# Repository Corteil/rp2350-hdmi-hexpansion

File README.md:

# Hexi-GFX — RP2350 HDMI Hexpansion for the EMF Tildagon Badge

A Tildagon hexpansion that mirrors the EMF badge's 240×240 round screen onto a
real HDMI/DVI monitor — an RP2350 drives the video over HSTX, pixel-doubled and
pillarboxed into a standard 640×480@60 signal. Every existing badge app gets
HDMI output with no code changes.

For the full design rationale, bench measurements, BOM, costing, and the
phase-by-phase delivery plan that got here, see [`HISTORY.md`](HISTORY.md).
This file covers what's true *now*.

## Status (03/10/26)

**Real mirroring and stable HSTX video work together, confirmed on real
hardware** — not just clean logs, actual moving content on a monitor. Current
firmware is `firmware/pio-testcard/`, running on an **Adafruit Metro RP2350**
dev board wired to a real badge hexpansion port, and since 03/10/26 also on
a **Raspberry Pi Pico 2 + Adafruit DVI Sock** (`-DHEXI_BOARD=pico2`, see
[its section](#alternative-bench-board-raspberry-pi-pico-2--adafruit-dvi-sock-tested)),
powered straight from the badge's 3V3. The custom hexpansion PCB's
schematic is drafted in `hardware/`; layout hasn't started (see
[Next step](#next-step)).

- Badge side: `display.attach_mirror()`, from a fork of
  [hazanjon/badge-2024-software](https://github.com/hazanjon/badge-2024-software)
  PR #454, with three real bugs found and fixed (SPI acquire-bus timeout, a
  non-idempotent display init that froze the badge's own screen, and an
  SPI-host/GPIO-pin ordering bug). Fixes were merged into hazanjon's
  `feature/hdmi-mirror` branch as
  [hazanjon/badge-2024-software#1](https://github.com/hazanjon/badge-2024-software/pull/1);
  that branch was rebuilt and flashed to the badge on 03/10/26 and the
  mirror was confirmed working with the Pico 2.
- RP2350 side: a from-scratch PIO-based SPI0 slave receiver (the hardware
  SPI0/PL022 peripheral loses byte alignment mid-burst on this chip and never
  recovers), double-buffered HSTX/DVI scanout, and a grey-to-black vignette
  fade on the pillarbox/mask area around the circular content.
- Known, understood, non-blocking: ~12% of frames (Metro) to ~18% (Pico 2,
  one sample) get abandoned when the badge starts a new frame before the
  RP2350 finishes the previous one — benign, fully instrumented, not a bug
  to fix.
- Known, benign: on the Pico 2 each port insertion resets the board twice
  about 2 s apart (likely the badge power-cycling the port); the mirror
  re-attaches by itself. The relay app's 500 ms wait before its own reset
  pulse (raised from 100 ms) made the automatic reset noticeably more
  reliable.

## Repo layout

| Path | What it is |
|---|---|
| `firmware/pio-testcard/` | **Current firmware.** Real HSTX/DVI video and real SPI mirror reception together — what's actually flashed to the bench Metro RP2350 today. |
| `firmware/testcard/` | Earlier milestone: full hexpansion-identity EEPROM emulation + the first end-to-end SPI link demo. Superseded by `pio-testcard` for the mirror path itself, but still the reference for EEPROM emulation. |
| `firmware/pin-probe/` | Pico 2 bench tool that counts transitions on every header GPIO (read over SWD), used with the badge's Pin Tester app to prove which Pico pin each `HS_F`..`HS_I` wire lands on. |
| `firmware/mirror_debug/` | Bench diagnostic tool used to bring up the PIO-based SPI slave receiver protocol. |
| `firmware/phase0-*/` | Individual bring-up experiments from early de-risking (HSTX/DVI basics, colour-channel fix, SPI speed sweep, EEPROM emulation, ctx rasterisation benchmark, microSD). Each has its own README. |
| `hdmi-mirror-plan.md` | Implementation notes for switching to hazanjon's real `attach_mirror()` protocol (SPI mode, byte order, per-port pin overrides). Completed; kept for reference. |
| `hdmi-stills-mode-plan.md` | Proposal (not built): a high-resolution stills mode and a second-screen mode, one new `TDHS` frame type. |
| `HISTORY.md` | The full design journal — rationale, bench measurements, BOM, costing, risk register, phase plan. Read this for *why*, not *what's true now*. |
| `hardware/` | KiCad 10 project for the hexpansion PCB (schematic v0.1 done, layout not started), `lib/jlc.*` (JLCPCB/LCSC symbols, footprints and 3D models), and `hexpansion_bom.xlsx`, the JLCPCB assembly BOM tracker. |
| `tildagon-base/` | Tildagon KiCad symbol and footprint library (hexpansion edge connector etc.), used by `hardware/`. |
| `bom.csv` | Machine-readable bill of materials, generated from the schematic (LCSC numbers, JLC Basic/Extended, prices). |

## Hardware today

Bench rig: an Adafruit Metro RP2350 (SPI0 slave on GPIO20–23, HSTX on
GPIO12–19), wired to a real hexpansion port on an EMF Tildagon badge.

**HS wiring gotcha (all ports):** hazanjon's badge-side `PORT_PINS` table
puts SCK on `HS_G` and CS on `HS_H`, the opposite of this project's original
`HS_G`=CS / `HS_H`=SCK convention. For a real mirror test, wire
`HS_F`→GPIO20, `HS_G`→GPIO22, `HS_H`→GPIO21, `HS_I`→GPIO23 at the RP2350 end.
First found on port 4, since tested on all six ports; the PCB is wired this
way. See `HISTORY.md` §4.1 for the full derivation and why the two sides
disagree.

VID/PID assigned for the eventual EEPROM-emulating hexpansion: `0x1969` /
`0x4544`.

### Alternative bench board: Adafruit Feather RP2350 + HSTX (builds, not yet tested on hardware)

Build with `-DHEXI_BOARD=feather` (see [Building and flashing](#building-and-flashing)).
The Feather is an RP2350A: the same die as the RP2354A the real hexpansion
uses (the RP2354A just adds 2 MB of flash in the package), and
its 22-pin HSTX FPC connector carries GPIO12–19 in the same lane order the
firmware already uses. So video needs no changes: plug in the same DVI
breakout and FPC cable as on the Metro.

Two things do move. GPIO21 is the Feather's onboard NeoPixel and isn't
broken out, so the Metro's GPIO20–23 SPI block can't be used. The
PIO-based receiver doesn't need hardware-SPI pins, just three consecutive
GPIOs for MOSI/CS/SCK, so it moves to D9–D11:

| Function | RP2350 GPIO | Feather pin |
|---|---|---|
| HSTX video (all 8 lines) | 12–19 | 22-pin HSTX FPC connector |
| SPI MOSI (`HS_F`) | 9 | D9 |
| SPI CS (`HS_H` on port 4) | 10 | D10 |
| SPI SCK (`HS_G` on port 4) | 11 | D11 |
| SPI MISO (`HS_I`, never driven) | 20 | MI |
| EEPROM-emulation I2C0 SDA / SCL | 4 / 5 | GPIO4 (CircuitPython `D12`/`IO4`) / D5 |
| Debug UART0 TX / RX (`_debug` build) | 0 / 1 | TX / RX |
| Status NeoPixel | 21 | onboard |
| `LS_A` → RUN | — | RST |
| GND | — | GND |

The port-4 SCK/CS crossover is already applied above. GPIO4 is labelled
from CircuitPython's pin map, so check the board silkscreen for that pad.
SWD is on the Feather's 3-pin JST-SH connector, so the Debug Probe cable
plugs straight in. UF2 flashing (hold BOOT, tap RESET) also works. Flash
is 8 MB, not 16 MB, which is plenty for this firmware. Use the RESET
button for step 3 of the manual reinsertion method below.

### Alternative bench board: Raspberry Pi Pico 2 + Adafruit DVI Sock (tested)

Build with `-DHEXI_BOARD=pico2`. **Confirmed working end to end on 03/10/26**:
stable mirror picture on the official Raspberry Pi monitor, status LED at
5 Hz while frames arrive. The Pico 2 is an RP2350A, so HSTX reaches the same
GPIO12–19 block the [Adafruit DVI Sock for Pico](https://www.adafruit.com/product/5957)
is wired to. The Sock is a passive connector plus 220 Ω series resistors, and
its product page describes it for the RP2040. It works fine with HSTX, but its
**lane order differs from the Metro/Feather wiring**, so this variant uses
`lane_to_output_bit = {0, 6, 4}` (D0 = GP12/13, D1 = GP18/19, D2 = GP16/17,
CK = GP14/15, "+" on the even GPIO).

| Function | RP2350 GPIO | Notes |
|---|---|---|
| HSTX video | 12–19 | DVI Sock, see lane order above |
| SPI MOSI (`HS_F`) | 0 | |
| SPI CS (`HS_H` on port 4) | 1 | |
| SPI SCK (`HS_G` on port 4) | 2 | port-4 SCK/CS crossover already applied |
| SPI MISO (`HS_I`, never driven) | 3 | |
| EEPROM-emulation I2C0 SDA / SCL | 4 / 5 | unchanged |
| 5V boost enable (active-high) | 6 | off at boot; the badge switches it, see [5V boost switch](#5v-boost-switch-added-151026) |
| Debug UART1 TX / RX (`_debug` build) | 8 / 9 | moved off GP0/1, which are now SPI inputs |
| Status LED (plain GPIO) | 25 | 1 Hz = running, no frames; 5 Hz = frames arriving |
| Status NeoPixel (external WS2812) | 22 | same colours as the other boards |
| `LS_A` → `RUN` | — | lets the badge reset the Pico 2; a reset switch from `RUN` to GND is also fitted |
| Badge 3V3 → VSYS (pin 39) | — | powers the board, with no USB attached |
| GND | — | shared with the badge: any GND pin on the port breakout hexpansion |

A step-by-step hardware build and flashing guide for this variant is in
[`docs/index.md`](docs/index.md), also published at
<https://corteil.github.io/rp2350-hdmi-hexpansion/>. A prebuilt UF2 is on the
[`pico2-v3` release](https://github.com/Corteil/rp2350-hdmi-hexpansion/releases/tag/pico2-v3).

Notes from bring-up:

- **Power:** it runs fine from the badge's 3V3 with no USB. Never connect USB
  and an external 3V3 into VSYS together: VBUS feeds VSYS through a diode, so
  the external source gets back-fed. Use a series Schottky if both are needed.
- **5 V on the Sock's 5 V pad** is monitor-dependent. Some monitors only show
  a signal when it is present; the official Raspberry Pi monitor and a video
  capture dongle don't need it. With no USB attached there is no VBUS, so for
  a monitor that needs it, use a boost converter: input from VSYS and GND,
  5 V output to the Sock's 5 V pad, GND common with the port breakout's GND.
- **Each port insertion resets the Pico 2 twice, about 2 s apart** (probably
  the badge power-cycling the port; not scoped). It is harmless: the mirror
  re-attaches and the picture returns by itself.
- **Wire-continuity check:** `firmware/pin-probe` plus Pin Tester's `blink`
  (via `mpremote exec`, store-installed path `/apps/Corteil_Pin_Tester`) maps
  each badge pin to a Pico GPIO. A bad `HS_F` wire here looked like CS/SCK
  arriving but a stuck-high or stuck-low data line and no `TDHD` match.

### Alternative bench board: Waveshare RP2350-PiZero (not yet tested)

The [Waveshare RP2350-PiZero](https://www.waveshare.com/wiki/RP2350-PiZero)
can stand in for the Metro, with one big caveat: its onboard mini-HDMI is
wired to **GPIO32–39**, and HSTX only reaches **GPIO12–19**, so the current
firmware can't drive the onboard connector. Instead, wire HSTX from the
40-pin header to an external DVI breakout, exactly as on the Metro.

Its chip (RP2350B), flash (W25Q128, 16 MB) and 12 MHz crystal match the
Metro, and every pin the firmware uses is on the header. The existing
`pio_testcard` build should therefore run unmodified, but that hasn't been
checked on real hardware yet.

**The header is not Raspberry-Pi numbered.** Waveshare's J5 net labels are
RP2350 GPIOs and differ from the silkscreen/BCM names (e.g. header pin 7 is
BCM4 but RP2350 **GPIO14**). Wire by *header pin number* from this table,
taken from Waveshare's schematic (`RP2350-PiZero.pdf`):

| Function | RP2350 GPIO | PiZero header pin |
|---|---|---|
| HSTX D2+ / D2− | 12 / 13 | 21 / 33 |
| HSTX CLK+ / CLK− | 14 / 15 | 7 / 29 |
| HSTX D1+ / D1− | 16 / 17 | 36 / 11 |
| HSTX D0+ / D0− | 18 / 19 | 12 / 35 |
| SPI MOSI (`HS_F`) | 20 | 38 |
| SPI CS (`HS_H` on port 4) | 21 | 40 |
| SPI SCK (`HS_G` on port 4) | 22 | 15 |
| SPI MISO (`HS_I`) | 23 | 16 |
| EEPROM-emulation I2C0 SDA / SCL | 4 / 5 | 8 / 10 |
| Debug UART0 TX / RX (`_debug` build) | 0 / 1 | 27 / 28 |
| GND | — | 6, 9, 14, 20, 25, 30, 34, 39 |
| `LS_A` → RUN | — | not on the header: solder to the RUN side of the reset button (Key2) |

HSTX lane assignment comes from `hstx_dvi_init()` in
`firmware/pio-testcard/src/main.c` (`lane_to_output_bit`), and the port-4
SCK/CS crossover above is already applied. Other differences from the Metro:

- **No addressable RGB LED.** The only LED is a red power LED. The firmware
  still drives its status-LED signal on GPIO25 (header pin 22). That's
  harmless, and you can wire a WS2812 there to get the status colours back.
- **SD card-detect isn't on a GPIO** (the slot's CD pin goes to GND), so
  GPIO22 is free for SCK.
- **Buttons:** Key1 is BOOTSEL and Key2 is reset (RUN). Use Key2 for step 3
  of the manual reinsertion method below.
- **SWD** is on the 3-pin header H1 (SWCLK / GND / SWDIO), so Debug Probe
  flashing works as documented. Holding Key1 while plugging in USB and
  copying `pio_testcard.uf2` also works.
- **Don't switch the build to the Pico SDK's `waveshare_rp2350_pizero` board
  file** without overriding its default UART. It puts UART1 on GPIO4/5,
  which collides with the EEPROM-emulation I2C in the `_debug` build. The
  Metro board file already used here puts UART0 on GPIO0/1.
- **Signal integrity:** the TMDS pairs are spread across the header, so they
  run at 252 Mbit/s over hand-run wires rather than an FPC cable. Keep each
  +/− pair short, equal-length and twisted together. Suspect the wiring
  first if the picture sparkles or drops out.

Using the onboard mini-HDMI would need one of two things. One is a PIO-based
PicoDVI scanout: 252 MHz `clk_sys`, a PIO block set to see GPIO16–47, and a
reworked framebuffer. The other is a board mod: remove the eight 200 Ω
series resistors (R1–R4, R6, R7, R10, R12) and feed GPIO12–19 into their
connector-side pads. Neither has been tried. The first diverges from the
HSTX design the hexpansion PCB will use.

## Reinsertion procedure (automatic since 11/10/26; manual fallback below)

Plugging the hexpansion into a running badge now brings the mirror up by
itself. The relay app packed into the fake EEPROM
(`firmware/testcard/badge_app/app.py`) runs on every insertion: it waits
500 ms for the connector to settle, pulses `LS_A` low for 10 ms to
hardware-reset the RP2350 (`LS_A` is wired to `RUN`), waits 1.5 s for it to
reboot, then calls `display.attach_mirror()`. See
`firmware/pio-testcard/src/main.c`'s own comments for the root-cause trail
on why a reset is needed at all.

- **Auto-attach setting.** The relay app reads the badge's
  `hdmi_auto_attach` setting (default on when unset) and skips both the
  reset and the attach when it's off. The setting is shared with
  [tildagon-hdmi-manager](https://github.com/Corteil/tildagon-hdmi-manager)
  (Info tile) and can also be toggled on the relay app's own screen (OK).
  Turning it on from the relay screen runs the same reset-then-attach.
- **Relay screen.** It shows `HDMI-HEX`, a live status from
  `display.is_mirror_active()` (green Mirroring, amber starting... / Not
  mirroring, red on failure, in the same colours as tildagon-hdmi-manager),
  the Auto-attach and 5V boost settings, and a key list (hexagonal buttons;
  OK is `C` and Cancel is `F` on this badge):

  | Key | Does |
  |---|---|
  | `B` | Toggle the 5V boost |
  | `C` | Toggle auto-attach (turning it on runs reset-then-attach) |
  | `D` | Attach / detach the mirror. Attaching does the reset first; detaching doesn't |
  | `F` | Back |

  Both the status and the reset need badge firmware with the display-mirroring
  patch; stock firmware has no `attach_mirror()`, so there the hexpansion is
  recognised but never mirrors.
- **In tildagon-hdmi-manager**, OK on the Status tile does the same
  detach, reset, wait, attach sequence on demand.

### 5V boost switch (added 15/10/26)

A 3V3→5V boost converter supplies the HDMI connector's +5V pin. Switching it
off saves power, so it is controlled from the badge:

- **Firmware.** `firmware/pio-testcard` drives the boost enable on GPIO6
  (`PIN_BOOST_EN` in `main.c`, active-high) from one control byte in the
  emulated EEPROM at address `0x20` (`EEPROM_CTRL_BOOST_EN`, bit 0; see
  `eeprom_i2c.h`). That is the gap between the 32-byte header and the
  filesystem at `0x40`, outside the header checksum. The badge reads and
  writes it as an ordinary EEPROM access at I2C address `0x50` with a 16-bit
  address. **The boost is off at boot and after every reset.**
- **Setting.** The badge-side setting is `hdmi_boost` (default on when unset),
  shared by the relay app (`B`) and tildagon-hdmi-manager (Info tile, "5V
  boost"). Both write the saved value to the firmware just before attaching and
  after each reset, so the boost comes on a moment after a reset and a
  setting of off stays off. With no badge app involved the +5V pin stays off,
  which some monitors may not tolerate.
- **Pin.** GPIO6 is the bench wiring. The planned PCB (pin map below, and
  `HISTORY.md`) puts the boost enable on GPIO29 and the Qwiic I2C1 on GPIO6/7,
  so `PIN_BOOST_EN` will need to follow whichever the board uses.

### Manual method (fallback)

If `LS_A` isn't wired to `RUN`, or the automatic reset misses, the original
manual sequence still works:

1. Insert the `HDMI-HEX` hexpansion.
2. In `tildagon-hdmi-manager` (or `display_manager`), **detach** the mirror.
3. Press the physical **reset button** on the RP2350 board (SW2 on the
   Metro; the reset button on your board otherwise).
4. **Attach** the mirror again from the same app.

The order matters: the reset goes between detach and attach, not after.

## Building and flashing

### RP2350 firmware (`pio-testcard`)

Needs the Raspberry Pi Pico SDK (2.x) and an `arm-none-eabi-gcc` toolchain,
with `PICO_SDK_PATH` set.

```sh
cd firmware/pio-testcard
mkdir -p build && cd build
cmake ..
cmake --build .
```

That builds for the Metro RP2350 (the default). For the Adafruit Feather
RP2350 + HSTX, configure a separate build directory from
`firmware/pio-testcard` instead:

```sh
cmake -B build-feather -DHEXI_BOARD=feather
cmake --build build-feather
```

For the Raspberry Pi Pico 2 + Adafruit DVI Sock, use `-DHEXI_BOARD=pico2`
the same way (`cmake -B build-pico2 -DHEXI_BOARD=pico2`).

Flash over SWD with a Raspberry Pi Debug Probe:

```sh
openocd -f interface/cmsis-dap.cfg -f target/rp2350.cfg -c "adapter speed 5000" \
  -c "program pio_testcard.elf verify reset exit"
```

### Badge-side driver

Depends on `display.attach_mirror()` from the fork above. Built via the
project's own Docker image (`ghcr.io/emfcamp/esp_idf:v5.5.1`):

```sh
git clone --recursive --branch pr-454-hazan-mirror https://github.com/Corteil/badge-2024-software.git
cd badge-2024-software
./scripts/firstTime.sh
docker run --rm --env "TARGET=esp32s3" -v "$(pwd)":/firmware -u "$(id -u):$(id -g)" \
  -e HOME=/tmp ghcr.io/emfcamp/esp_idf:v5.5.1
```

Flash to a real badge in bootloader mode (disconnect USB, hold **BAT + BOOP**
for ~20s, reconnect):

```sh
docker run --rm --device /dev/ttyACM0:/dev/ttyUSB0 --group-add <your dialout/plugdev GID> \
  --env "TARGET=esp32s3" -v "$(pwd)":/firmware -u "$(id -u):$(id -g)" -e HOME=/tmp \
  ghcr.io/emfcamp/esp_idf:v5.5.1 deploy
```

The badge stays in bootloader mode after flashing — disconnect/reconnect the
USB cable once more to actually boot the new image.

## Next step

Designing the actual hexpansion PCB (44 mm hexagon, EEPROM emulation, USB-C +
HDMI power isolation) — the whole plan for it, including the pin map, power
architecture, BOM, and costing this bench work was de-risking, is in
[`HISTORY.md`](HISTORY.md).

**Schematic v0.1 is done** (`hardware/rp2350-hdmi-hexpansion.kicad_sch`,
28/09/26). The PCB layout hasn't started: open the project and run
*Tools → Update PCB from Schematic*. Every part has a JLCPCB/LCSC number,
and its symbol, footprint and 3D model are in the project library
`hardware/lib/jlc.*`, pulled with
[easyeda2kicad](https://github.com/uPesy/easyeda2kicad.py). KiCad's ERC is
clean apart from one expected warning (HEXP_DET tied to GND is how the
badge detects a hexpansion), and the exported netlist was checked
pin-for-pin against the design. `bom.csv` and `hardware/hexpansion_bom.xlsx`
are generated from the schematic.

Changes from the `HISTORY.md` plan:

- **MCU is the RP2354A**, not the RP2350A: the same die and QFN-60 pinout,
  with 2 MB of flash in the package on QSPI CS0. There's no external flash
  chip (the W25Q128 is gone). 2 MB is plenty: the largest firmware build is
  about 260 KB. Build with `PICO_FLASH_SIZE_BYTES` set to 2 MB.
- **The PSRAM is footprint-only (DNP)**, for optional hand soldering. The
  part is the **APS6404L-3SQR-SN** (SOP-8, 3.3 V); the `-ZR` that the old
  BOM listed is USON-8. It stays on QSPI CS1 = GPIO0, with a 10k pull-up on
  CS that is fitted even when the PSRAM isn't, so firmware must detect it
  at boot rather than assume it.
- **Full-size HDMI Type A** socket instead of mini-HDMI. It's wider, so check
  the fit on the outer flat.
- **One Qwiic socket** instead of two, to save edge space.
- **TLV62569** 2 A buck instead of the TPS62203 (300 mA, poor stock).
- **No HDMI DDC/EDID.** The output is always 640×480@60, which every
  monitor must accept, so there's nothing to read. The PCA9306 and its six
  passives are gone. Hot-plug detect stays (GPIO2).
- **No microSD.** That frees the second side flat and GPIO5 and 8–11.
  Spare GPIOs are now **3, 4, 5, 8, 9, 10, 11**, all left no-connect.
- **Trimmed to the Raspberry Pi minimal design.** TMDS lines go straight
  from GPIO12–19 to the ESD chips and socket, with no 0R insurance resistors,
  as the bench has always run. There are 7 × 100 nF on 3.3 V (pins 44/45 and
  53/54 share, as in Raspberry Pi's reference), no BOOTSEL pull-up (QSPI_SS
  has one internally) and no RUN debounce cap. The ferrite beads are gone.
- Kept from the design guide: the 1k crystal series resistor, 33R
  VREG_AVDD filter, 27R USB series resistors and a 10k RUN pull-up (because
  of the badge reset). Also added: an HDMI +5V PTC fuse and test pads.
- Result: **80 JLC-placed parts, about $5.11 a board** at the 10-board price
  tier (25 capacitors, 32 resistors).

**Pin map changes from `HISTORY.md` §4.1.** It had no free GPIOs for three
signals, so `LS_C`/`LS_D`/`LS_E` are left unconnected and their GPIOs reused:

| GPIO | Now | Was |
|---:|---|---|
| 27 | SK6805 RGB LED data | `LS_C` (bootloader-entry idea) |
| 28 | Badge-rail sense (ADC2, 100k/100k from `3V3_BADGE`) | `LS_D` spare |
| 29 | HDMI +5V boost enable (100k pull-down) | `LS_E` spare |

On the board, `HS_G`→GPIO22 (SCK) and `HS_H`→GPIO21 (CS). That's the
crossing the badge's mirror driver needs, **tested on all six ports**.

**Firmware changes the PCB needs** (from `pio-testcard`): EEPROM emulation
moves from GPIO4/5 to **GPIO24/25**, with its internal pull-ups *off*
(they'd back-power an unpowered badge). The status NeoPixel moves to
**GPIO27**. Set the flash size to 2 MB.

**Badge reset without backfeed.** `LS_A` drives RUN through **U11, an
SN74LVC1G07 open-drain buffer powered from `3V3_BADGE`**. R4 (10k to
`3V3_BADGE`) holds `LS_A` high, so it idles at "not reset". When the badge
is off, U11 is unpowered. Its partial-power-down (I_off) spec, ≤10 µA and
typically far less, stops the RUN pull-up leaking into the badge, and the
RP2354A keeps running from USB. A plain diode can't do this: the reset
current and the leak flow the same way.

## Acknowledgements

This project depends on the work of [hazanjon](https://github.com/hazanjon).
The badge-side display mirroring that the hexpansion receives, including
`display.attach_mirror()`, the SPI frame protocol with its `TDHD` header, and
the per-port pin handling in `flow3r_bsp_display_mirror.c`, comes from
his [badge-2024-software](https://github.com/hazanjon/badge-2024-software)
work (PR #454 against `emfcamp/badge-2024-software`). His
[display_manager](https://github.com/hazanjon/display_manager) app provides
the badge-side driver definitions and attach controls used to drive it.
Without that groundwork there would be nothing for this hexpansion to mirror,
and the fixes in this repo's badge-side PR were built on top of it. Thank you.

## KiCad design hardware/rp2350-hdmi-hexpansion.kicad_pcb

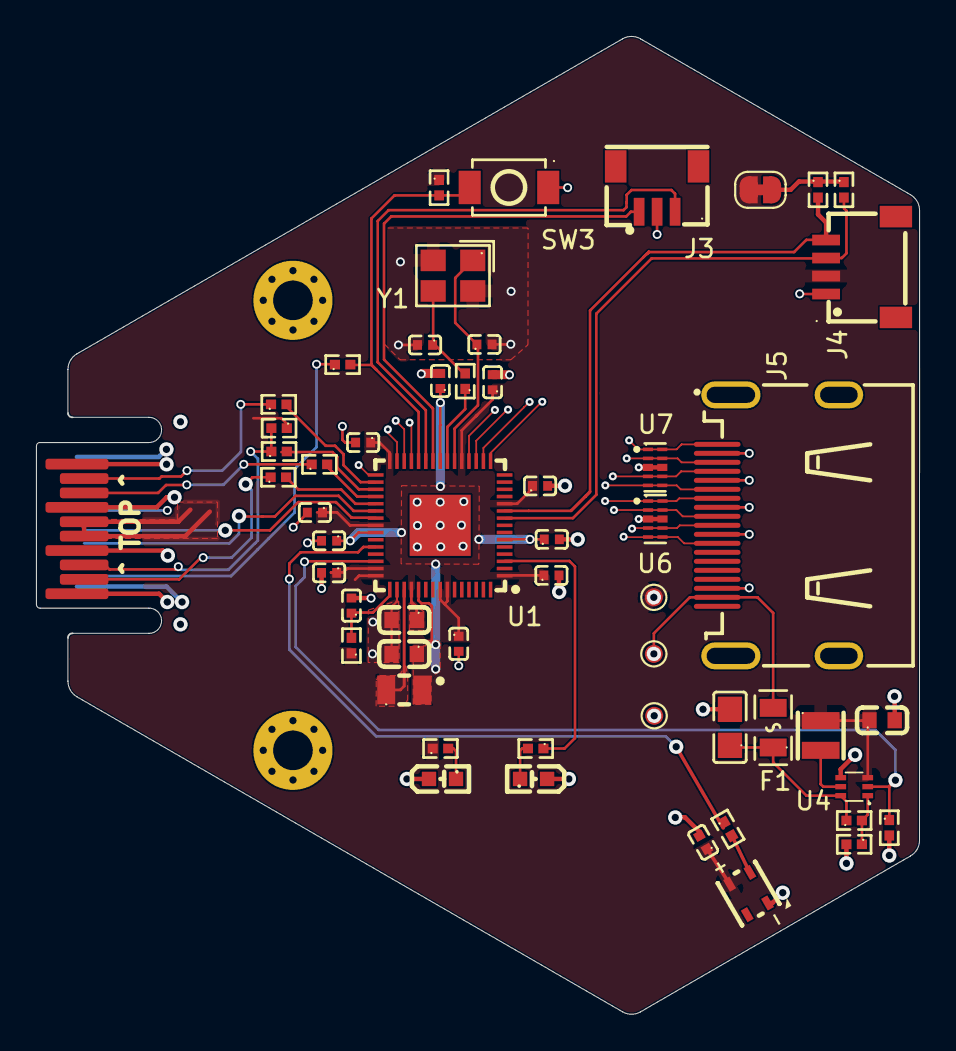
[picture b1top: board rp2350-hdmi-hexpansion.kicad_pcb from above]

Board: 4 copper layers, 49.1 x 54.3 mm, 57 parts (0 on the bottom side), 43 nets.

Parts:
C1, C2, C3, C4, C5, C6, C7, C10, C11, C12, C32: 100nF; C0402
C13, C14: 4.7uF; C0603
C15: 4.7uF; C0402
C17, C18: 15pF; C0402
C25: 10uF; C0603
C26: 22uF; C0805
F1: 200mA PTC; F0805
H1, H2: MountingHole; MountingHole_2.2mm_M2_Pad_Via
J1: Hexpansion-Connector; hexpansion-edge-connector
J3: SWD; CONN-SMD-3P-P1.00_BM03B-SRSS-TB-LF-SN
J4: Qwiic; CONN-SMD_4P-P1.00_SM04B-SRSS-TB-LF-SN
J5: HDMI-A; HDMI-SMD_19P-P0.50-H-F
JP1: Qwiic pull-ups; SolderJumper-2_P1.3mm_Bridged_RoundedPad1.0x1.5mm
L1: 3.3uH; IND-SMD_L2.0-W1.6_AOTA-B201610S3R3-101-T
L3: 1uH; IND-SMD_L2.5-W2.0_FTC252010S
LED1: PWR; LED-SMD_L1.6-W0.8-R-RD
LED2: STATUS; LED-SMD_L1.6-W0.8-R-RD
LED3: SK6805; LED-SMD_4P-L2.7-W2.4_SK6805MICRO-J
R1, R36, R37, R38, R39: 33R; R0402
R2, R51, R53: 1k; R0402
R3, R41: 10k; R0402
R18: 100k; R0402
R19: 200k; R0402
R20: 27k; R0402
R48, R49, R50: 4.7k; R0402
R52: 330R; R0402
SW3: RESET; SW-SMD_L3.9-W3.0-P4.45
TP1: +3V3; TestPoint_Pad_D1.0mm
TP2: V5_HDMI; TestPoint_Pad_D1.0mm
TP3: GND; TestPoint_Pad_D1.0mm
U1: RP2354A; QFN-60_L7.0-W7.0-P0.40-TL-EP3.4
U4: TPS61023DRLR; SOT-563_L1.6-W1.2-P0.50-LS1.6-BR
U6, U7: TPD4E05U06; USON-10_L2.5-W1.0-P0.50-BL
Y1: 12MHz; CRYSTAL-SMD_4P-L3.2-W2.5-BL

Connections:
+3V3: C1.1, C2.1, C3.1, C4.1, C5.1, C6.1, C7.1, C14.1, C25.1, C32.1, J1.15 (3V3), J1.16 (3V3), J4.2, JP1.1 (A), L3.1, LED3.3 (VDD), R1.1, R3.1, R41.1, R50.1, TP1.1 (1_1), U1.1 (IOVDD), U1.11 (IOVDD), U1.20 (IOVDD), U1.30 (IOVDD), U1.38 (IOVDD), U1.44 (ADC_AVDD), U1.45 (IOVDD), U1.49 (VREG_VIN), U1.53 (USB_OTP_VDD), U1.54 (QSPI_IOVDD), U4.3 (VIN)
/BADGE_SCL: J1.5 (SCL), U1.37 (GPIO25)
/BADGE_SDA: J1.4 (SDA), U1.36 (GPIO24)
/BOOST_EN: R18.1, U1.43 (GPIO29_ADC3), U4.2 (EN)
/BOOST_FB: R19.2, R20.1, U4.1 (FB)
/BOOST_SW: L3.2, U4.5 (SW)
/DVDD: C10.1, C11.1, C12.1, C13.1, L1.2, U1.6 (DVDD), U1.23 (DVDD), U1.39 (DVDD), U1.50 (VREG_FB)
/HDMI_CK_N: J5.12 (TMDSClock-), U1.19 (GPIO15), U6.5 (D2-), U6.6 (NC)
/HDMI_CK_P: J5.10 (TMDSClock+), U1.18 (GPIO14), U6.4 (D2+), U6.7 (NC)
/HDMI_D0_N: J5.9 (TMDSData0-), U1.31 (GPIO19), U6.2 (D1-), U6.9 (NC)
/HDMI_D0_P: J5.7 (TMDSData0+), U1.29 (GPIO18), U6.1 (D1+), U6.10 (NC)
/HDMI_D1_N: J5.6 (TMDSData1-), U1.28 (GPIO17), U7.5 (D2-), U7.6 (NC)
/HDMI_D1_P: J5.4 (TMDSData1+), U1.27 (GPIO16), U7.4 (D2+), U7.7 (NC)
/HDMI_D2_N: J5.3 (TMDSData2-), U1.17 (GPIO13), U7.2 (D1-), U7.9 (NC)
/HDMI_D2_P: J5.1 (TMDSData2+), U1.16 (GPIO12), U7.1 (D1+), U7.10 (NC)
/HS_F: J1.12 (HS_F), R36.1
/HS_G: J1.13 (HS_G), R38.1
/HS_H: J1.18 (HS_H), R37.1, R41.2
/HS_I: J1.19 (HS_I), R39.1
/LED1_A: LED1.1 (A), R50.2
/LED2_A: LED2.1 (A), R51.2
/LED_STATUS: R51.1, U1.3 (GPIO1)
/LS_A: J1.2 (LS_A), R53.1
/QWIIC_PU: JP1.2 (B), R48.1, R49.1
/QWIIC_SCL: J4.4, R49.2, U1.10 (GPIO7)
/QWIIC_SDA: J4.3, R48.2, U1.9 (GPIO6)
/RGB_DIN: R52.1, U1.41 (GPIO27_ADC1)
/RUN: R3.2, R53.2, SW3.1, U1.26 (RUN)
/SPI_CS: R37.2, U1.33 (GPIO21)
/SPI_MISO: R39.2, U1.35 (GPIO23)
/SPI_MOSI: R36.2, U1.32 (GPIO20)
/SPI_SCK: R38.2, U1.34 (GPIO22)
/SWCLK: J3.1, U1.24 (SWCLK)
/SWDIO: J3.3, U1.25 (SWDIO)
/V5_BOOST: C26.1, F1.1, R19.1, U4.6 (VOUT)
/V5_HDMI: F1.2, J5.18 (+5VPower), TP2.1 (1_1)
/VREG_AVDD: C15.1, R1.2, U1.46 (VREG_AVDD)
/VREG_LX: L1.1, U1.48 (VREG_LX)
/XIN: C17.1, U1.21 (XIN), Y1.1
/XOUT: R2.1, U1.22 (XOUT)
/XOUT_XTAL: C18.1, R2.2, Y1.3
GND: C1.2, C2.2, C3.2, C4.2, C5.2, C6.2, C7.2, C10.2, C11.2, C12.2, C13.2, C14.2, C15.2, C17.2, C18.2, C25.2, C26.2, C32.2, H1.1 (1_1), H2.1 (1_1), J1.1 (GND), J1.6 (HEXP_DET), J1.10 (GND), J1.11 (GND), J1.14 (GND), J1.17 (GND), J1.20 (GND), J3.2, J4.1, J5.2 (TMDSData2Shield), J5.5 (TMDSData1Shield), J5.8 (TMDSData0Shield), J5.11 (TMDSClockShield), J5.17 (DDC/CECGround), J5.20, J5.21, J5.22, J5.23, LED1.2 (K), LED2.2 (K), LED3.1 (GND), R18.2, R20.2, SW3.2, TP3.1 (1_1), U1.47 (VREG_PGND), U1.61 (EP), U4.4 (GND), U6.3 (GND), U6.8 (GND), U7.3 (GND), U7.8 (GND), Y1.2 (GND), Y1.4 (GND)
unnamed: LED3.2 (DIN), R52.2

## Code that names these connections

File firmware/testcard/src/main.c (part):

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// wire format and bandwidth profile the real thing needs either way.
//
// Board: Metro RP2350 -- same bench rig as A2/C3/C4 (I2C0 on GPIO4/5,
// SPI0 on GPIO20-23) and phase0-dvi-colorfix (HSTX on GPIO12-19, its own
// dedicated 22-pin connector). All three pin groups are disjoint, so one
// physical board runs the whole demo.
//
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        2u << HSTX_CTRL_CSR_SHIFT_LSB |
        HSTX_CTRL_CSR_EN_BITS;

    // Metro's HSTX port: CKP/CKN=GPIO14/15, D0P/D0N=GPIO18/19,
    // D1P/D1N=GPIO16/17, D2P/D2N=GPIO12/13 -- silicon-fixed, same as the
    // Feather (HSTX bit index n is always GPIO 12+n).
    hstx_ctrl_hw->bit[2] = HSTX_CTRL_BIT0_CLK_BITS;
    hstx_ctrl_hw->bit[3] = HSTX_CTRL_BIT0_CLK_BITS | HSTX_CTRL_BIT0_INV_BITS;
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// ----------------------------------------------------------------------------
// SPI0 slave: row-streaming mirror link -- mode 3 (CPOL=1, CPHA=1), CS
// held low per row, the protocol proven in Phase 0 A2/C3
// (firmware/phase0-a2-spi/). Pin roles: HS_F=MOSI(GPIO20),
// HS_G=CS(GPIO21), HS_H=SCK(GPIO22), HS_I=MISO(GPIO23) -- main README
// section 4.1's resolved role assignment.
//
// One SPI burst per FRAME (all 240 rows, 115,200 bytes), not per row --
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
#define SPI_PORT     spi0
#define PIN_MOSI     20
// Reverted (2026-09-10): GPIO21/22 are NOT freely reassignable between
// SCK/CS via software -- README §4.1's HS_G=CS(GPIO21)/HS_H=SCK(GPIO22)
// role assignment is a hardware-fixed fact about this RP2350's own GPIO
// function-select table (confirmed against real silicon, §9 risk 19),
// not a convention this code chose. gpio_set_function(pin, GPIO_FUNC_SPI)
// only selects WHICH peripheral claims a pin, not which signal within
// that peripheral it becomes -- GPIO21 is always SPI0's SSn/CS input and
// GPIO22 is always its SCLK input, regardless of what these #defines are
// named. The earlier "swap to match hazanjon's PORT_PINS labeling" edit
// didn't actually swap anything electrically; it just made this file
// call the wrong pin by the wrong name, so hazanjon's real SCK signal
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
// ----------------------------------------------------------------------------

// Heartbeat/activity LED via the Metro's onboard NeoPixel (GPIO25) --
// GPIO23 (PICO_DEFAULT_LED_PIN on this board) is unusable here, already
// claimed as SPI0's MISO, and a plain GPIO needs an LED wired up to be
// visible at all, whereas the NeoPixel is already on the board. Uses
// pico-sdk's own official ws2812.pio program (BSD-3, Raspberry Pi) via
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
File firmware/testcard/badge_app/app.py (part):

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# streams it over the same link at the same bandwidth the real thing
# needs, which is what actually exercises the pipeline end to end.
#
# SPI: config.pin (hs_1..4 -- HS_F=MOSI, HS_G=CS, HS_H=SCK, HS_I=MISO,
# main README section 4.1's resolved role assignment), mode 3 (CPOL=1,
# CPHA=1), matching the RP2350 SPI0-slave protocol proven in Phase 0
# A2/C3 (firmware/phase0-a2-spi/).
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# No sck/mosi/cs/dc override (2026-09-10 -> superseded 2026-09-20):
# hazanjon's PORT_PINS table (badge-2024-software feature/hdmi-mirror,
# flow3r_bsp_display_mirror.c) disagreed with this repo's own README
# §4.1 role assignment for GPIO21/22 (SCK vs CS swapped) -- resolved by
# physically rewiring the bench connection instead (HS_G/HS_H swapped to
# the RP2350's GPIO22/GPIO21 respectively), see main.c's own
# PIN_SCK/PIN_CS comment. An early version of this file also overrode
# `dc` (to GPIO6) after port 1's default dc pin (GPIO42 = HS_I = the
# RP2350's SPI0 MISO line) crashed the badge on attach with the OLD
# synthetic driver dict -- proven no longer needed: today's real
# HDMI_DRIVER dict (see _attach() below) attaches cleanly on port 1 with
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class MirrorApp(app.App):
    def _reset_rp2350(self):
        # Pulse LS_A low to hardware-reset the RP2350 -- HISTORY.md section
        # 4.2's own documented pin table: "RUN pin <- LS_A (badge-controlled
        # reset) and SW2 reset button" (cross-checked against two
        # independent real hexpansion designs). Requires LS_A physically
        # wired to the Metro's RUN pin on the bench rig -- if it isn't,
        # this just prints and does nothing (no exception propagates).
        #
        # Added 2026-09-20: reinsertion sometimes left the RP2350's
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        # entirely, matching the project's own always-intended pin design
        # rather than chasing the exact HSTX fault from the badge side.
        try:
            ls_a = self.config.ls_pin[0]
            ls_a.init(ls_a.OUT)
            ls_a.value(0)
            time.sleep_ms(10)
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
